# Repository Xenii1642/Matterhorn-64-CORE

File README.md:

Matterhorn 64 CORE is the world's smallest open-source Nintendo 64 motherboard redesign. 
It utilizes components taken from an original Nintendo 64 console. 
Because it does **not** rely on emulation, it works perfectly with all games released on the system. 

This board redesign enables smaller, better, cleaner and more reliable Nintendo 64 based builds. 
Matterhorn 64 CORE can easily be integrated in different kinds of builds such as Nintendo 64 portable devices or mini consoles. 

It is fully open-source and released under the CERN-OHL-S-2.0 license. 

## Features
The Matterhorn 64 CORE redesign:
- The world's smallest open source Nintendo 64 motherboard
- Fits in a tiny 78x77.2 mm form factor 
- Runs on real hardware, **no emulation**
- 100% compatible with **all** games released on the system, including flashcarts
- Runs on 3.3V @2A 
- Designed using KiCad 9
- Layout and routing is optimized and clean, making it easy to use in future Nintendo 64 builds
- 100% open-source and released under the CERN-OHL-S-2.0 license

## Compatibility
### General compatibility
Due to the complexity of the Nintendo 64 hardware, some of its features are not available on this design. 
Please note that:
- The console is compatible with both NTSC and PAL components. However, it is **NOT** region free. It will only accept games released on the same region as the donor board.
- The console does accept memory expansion, but it is not natively compatible with the orignal Expansion Pak cartridge. You'll need to solder two RDRAM36 4MB instead of the two RDRAM18 2MB chips present by default on the console in order to enable the Expansion Pak.
- The console does **NOT** have any video output system. You'll either need to hook up an original composite encoder compatible with your region or an HDMI kit.
- The console does **NOT** have on-board voltage regulators. An additional N64 PSU or 3.3V PSU will be needed in order to use it. The console requires only requires 3.3V at 2A, but please consider that some HDMI mod or composite encoders may require 5V as well.
- The console is compatible with original controllers.
- It is also compatible with original cartridges using the breakout board.

### Nintendo 64 donor board revision compatibility
This mod is **ONLY** compatible with the following motherboard revisions:
#### NTSC Revisions (North America and Japan)
- NUS-CPU-01 (Japan only - 1996)
- NUS-CPU-02 (1996)
- NUS-CPU-03 (1996)
- NUS-CPU-04 (1996-1997)
- NUS-CPU-05 (1997)
- NUS-CPU-05-1 (1997)
- NUS-CPU-06 (1998)
- NUS-CPU-07 (1998)

#### PAL REVISION (Europe and Australia)
- NUS-CPU(P)-01 (1996)
- NUS-CPU(R)-01 (France only - 1997)

**ANY NEWER REVISION WILL NOT BE COMPATIBLE**

## Disclamer
This project requires complex soldering techniques. It relies on small pitch QFPs and 0402 passives.
Removing the components from the original board can cause irreparable damage if done incorrectly.

Due to the nature of this project, I am not responsible for any physical damages that may occur. 

## PCB Files
The Matterhorn 64 CORE motherboard has been entirely designed using KiCad 9. 
All the files are available in the [KiCad files folder](https://github.com/Xenii1642/Matterhorn-64-CORE/tree/main/KiCad%20Files) of this repository. 
The libraries created are also available in that same folder. 

Gerbers can be found in the [Gerber folder](https://github.com/Xenii1642/Matterhorn-64-CORE/tree/main/Gerbers). 

The console needs those two PCBs in order to make it work:
- [Matterhorn 64 CORE redesign](https://github.com/Xenii1642/Matterhorn-64-CORE/blob/main/Gerbers/Matterhorn-64-CORE.zip)
- [Matterhorn Cartridge Breakout](https://github.com/Xenii1642/Matterhorn-64-CORE/blob/main/Gerbers/Cartridge-Breakout-Board.zip)

The CORE itself represents the main logic of the console. The breakout board is used easily connect a full size game cartridge to the console. 

## Ordering
For this project, I recommend ordering the board through [JLCPCB](https://jlcpcb.com/) or [PCBWay](https://pcbway.com/). 
I personally ordered mine through [JLCPCB](https://jlcpcb.com/). 

You'll find here the list of settings that must be applied when ordering. 

### [Matterhorn 64 CORE](https://github.com/Xenii1642/Matterhorn-64-CORE/blob/main/Gerbers/Matterhorn-64-CORE.zip)
- Material: FR4
- Layers: 4
- Thickness: 1.6mm
- Specify Stackup: YES - JLC04161H-3313
- Impedance Control: ±10%
- Stencil: recommended but not obligatory.

### [Matterhorn Cartridge Breakout](https://github.com/Xenii1642/Matterhorn-64-CORE/blob/main/Gerbers/Cartridge-Breakout-Board.zip)
- Material: FR4
- Layers: 2

### Board Impedance Control
As you might notice, the CORE requires controlled impedance. 
The Nintendo 64 uses an extremely fast Rambus Dynamic Random Access Memory Bus (RDRAM BUS). 
In order to work, the CORE requires controlled impedance to match the 50Ω required by the RDRAM BUS. 

The Gerber files for this board include an Excel document which specifies which traces require those controlled impedance. 
This document will only be taken into account by JLCPCB if the order specifies the use of the "Controlled Impedance" option set to ±10%.

Please note that the board **might** work by using the 3313 stackup with no controlled impedance. 
To make sure my prototype was working, I did order it using those specifications. 
Ordering without it has not been tried and is at your own risks. 

All the components are listed in the Bill Of Materials (BOM). They can be ordered through Digikey or Mouser. 

## Assembly 
Once you've sourced a working Nintendo 64 console, a few games to test it, all the components and the Matterhorn 64 CORE boards, assembly can begin!
First of all, you'll need to access the Nintendo 64 motherboard and remove these components:
- CPU-NUS (U10)
- RCP-NUS (U9)
- 2x RDRAM18-NUS (U14 & U11) (or 1x RDRAM36 depending of the version, U14)) 
- NUS-PIF (U6)
- PTS9128 (U3)
- 74LCV125 (U8)
- 2x MX8330 (U7 & U15)
- 2x Crystals (X1 & X2)
- Sharp 7VZ5 LDO (U12)
- Cartridge slot (P5)

Source of this image: Wikipedia.com

I personally removed mine using hot air and a bit of flux. I heated at 360°C. 
Once removed, they can take place on the new motherboard. 
Low melting solder is not recommended in this process since the board will heat and cool down constantly when running, which can damage the solder joints after a long time. It is also not recommended to heat either the board or the components too much, which could lead to issues. 
I recommend soldering the whole front side and then solder the back side. 

The breakout board is much simpler, it only has a single FFC connector and the cartridge slot, which are much easier to solder than the little passives in my opinion. 

Once everything is done and cleaned using isopropyl alcohol, the test process can begin!

## Testing
First, connect the breakout board and make sure you don't have any dead shorts between the 3.3V line and the GND. 
Then, insert a game and power it up! The board is properly powered if:
- The console draws roughly 1.4A
- Vterm shows 2.55V
- Vref shows 1.91V

If you own a logic analyzer, you can connect it to the audio data pins or controller ports.
This is what you should see on the controller data line when a controller is plugged on Super Mario 64

Please note that those signals **DO NOT** appear if the game is not properly read.
If everything seems good, you can hook up an HDMI mod or composite encoder and test it out! If it displays, it works! Great job!

## Known issue:
When I assembled my prototype, I *probably* heated the CPU too much while removing it. This caused the console to only work if heated.
More tests will be done to understand what exactly caused that. 

However I want to mention that the board works flawlessly for multiple consecutive days. 

## Future projects
This board is my official entry into Nintendo 64 modding. 
I'm working on two big projects which both use the CORE:
- Weisshorn 64 Mini: A collab between SenorAvocado and the Xii-Labs to create a Nintendo 64 Classic Mini console.
- Matterhorn 64: An ultimate Nintendo 64 portable. It's going to be a true revolution, also powered by the core.

Going to keep everyone update through my socials and the BitBuilt server. 

## Credits
This project was the most complicated I've done. Thankfully some members of the BitBuilt community helped me out to make my journey easier.
Therefore, I wanted to address big thanks to:
- @cy-888 who collaborated with me on some part of the design, especially footprints
- @CrazyGadgetMods who made great open-source flexes which helped me understanding some part of the console
- @mackieks who answered all my technical questions and took the time to review the whole board
- @thedrew and @gunnar who gave me insiparation to design my own motherboard recreation as long as helping me throughout the process.

## Media
You can find a video of my working board on my Instagram account:
[Matterhorn 64 CORE testing video](https://www.instagram.com/reel/DWvlAQKiPuf/)

I've also considered making a longer YouTube video on the subject. I will probably do it when I have more time.
## License
Matterhorn 64 CORE is released under the CERN-OHL-S-2.0 license. 
This license allows you to:
- Study
- Modify
- Manufacture
- Sell
- Distribute

Any modified versions of derivatives must also remain open-source under **the same, unmodified license**
You must also properly credit the original creators when reusing or redistributing these files.

## Support
If you notice anything wrong with the design, please let me know!
You can also reach to me for questions or general help, I'm always happy to help 👍

Thank you for your support and see you next time!

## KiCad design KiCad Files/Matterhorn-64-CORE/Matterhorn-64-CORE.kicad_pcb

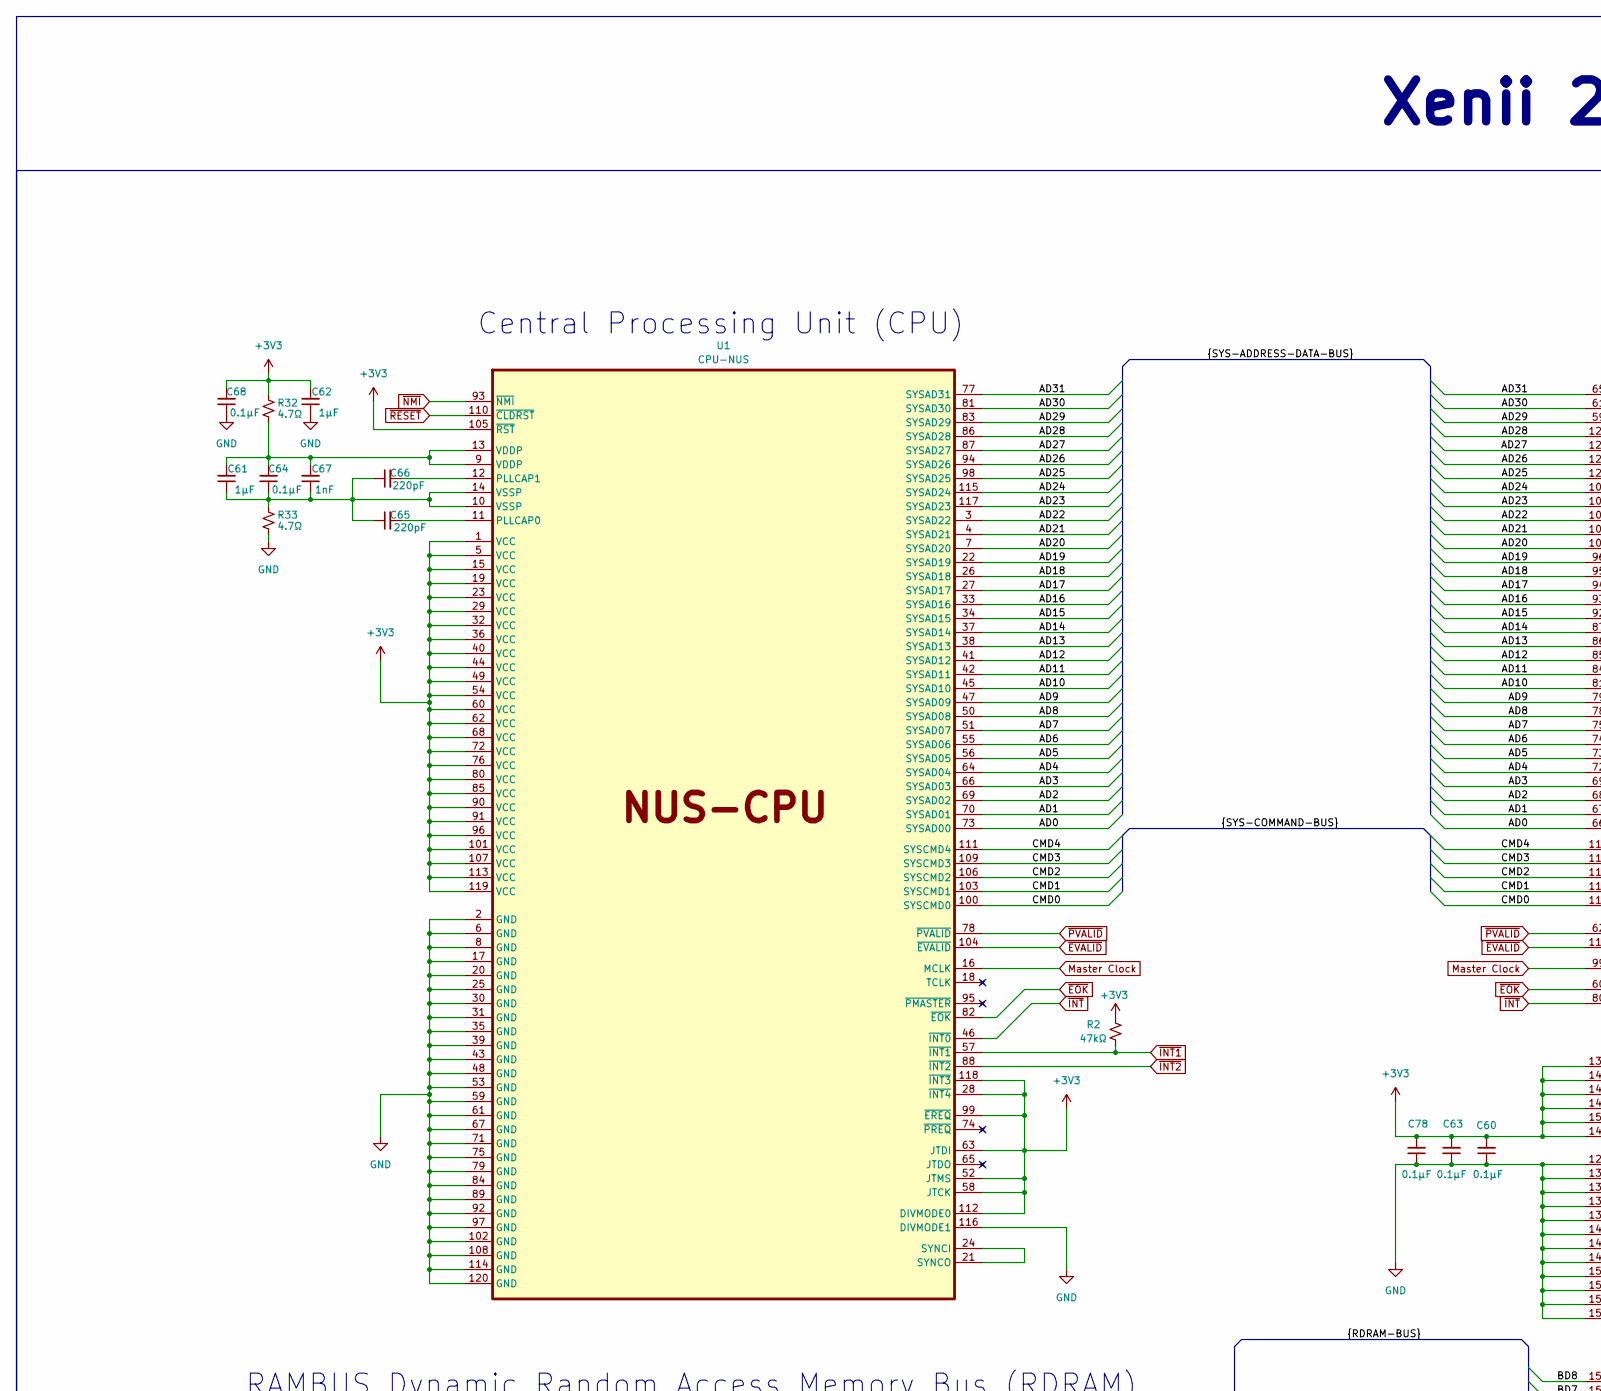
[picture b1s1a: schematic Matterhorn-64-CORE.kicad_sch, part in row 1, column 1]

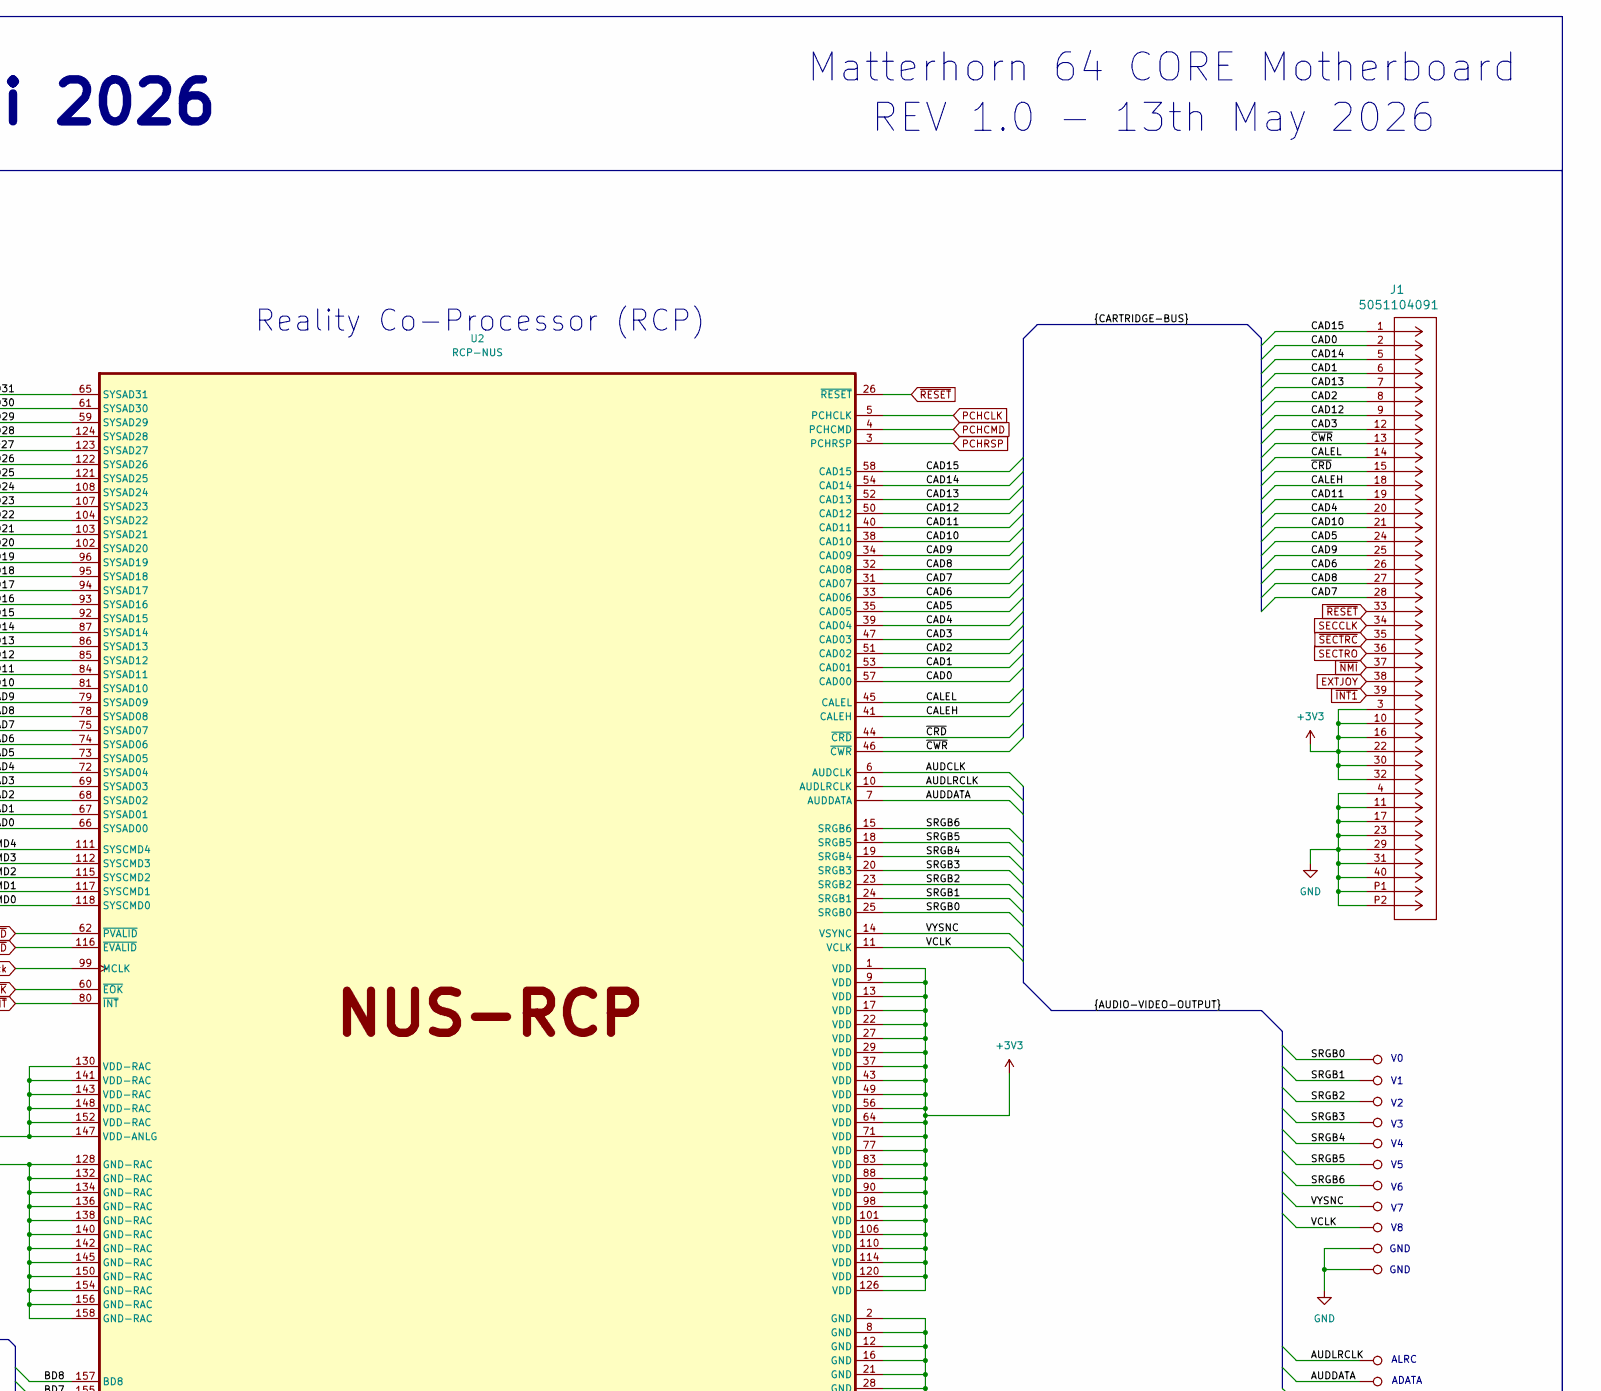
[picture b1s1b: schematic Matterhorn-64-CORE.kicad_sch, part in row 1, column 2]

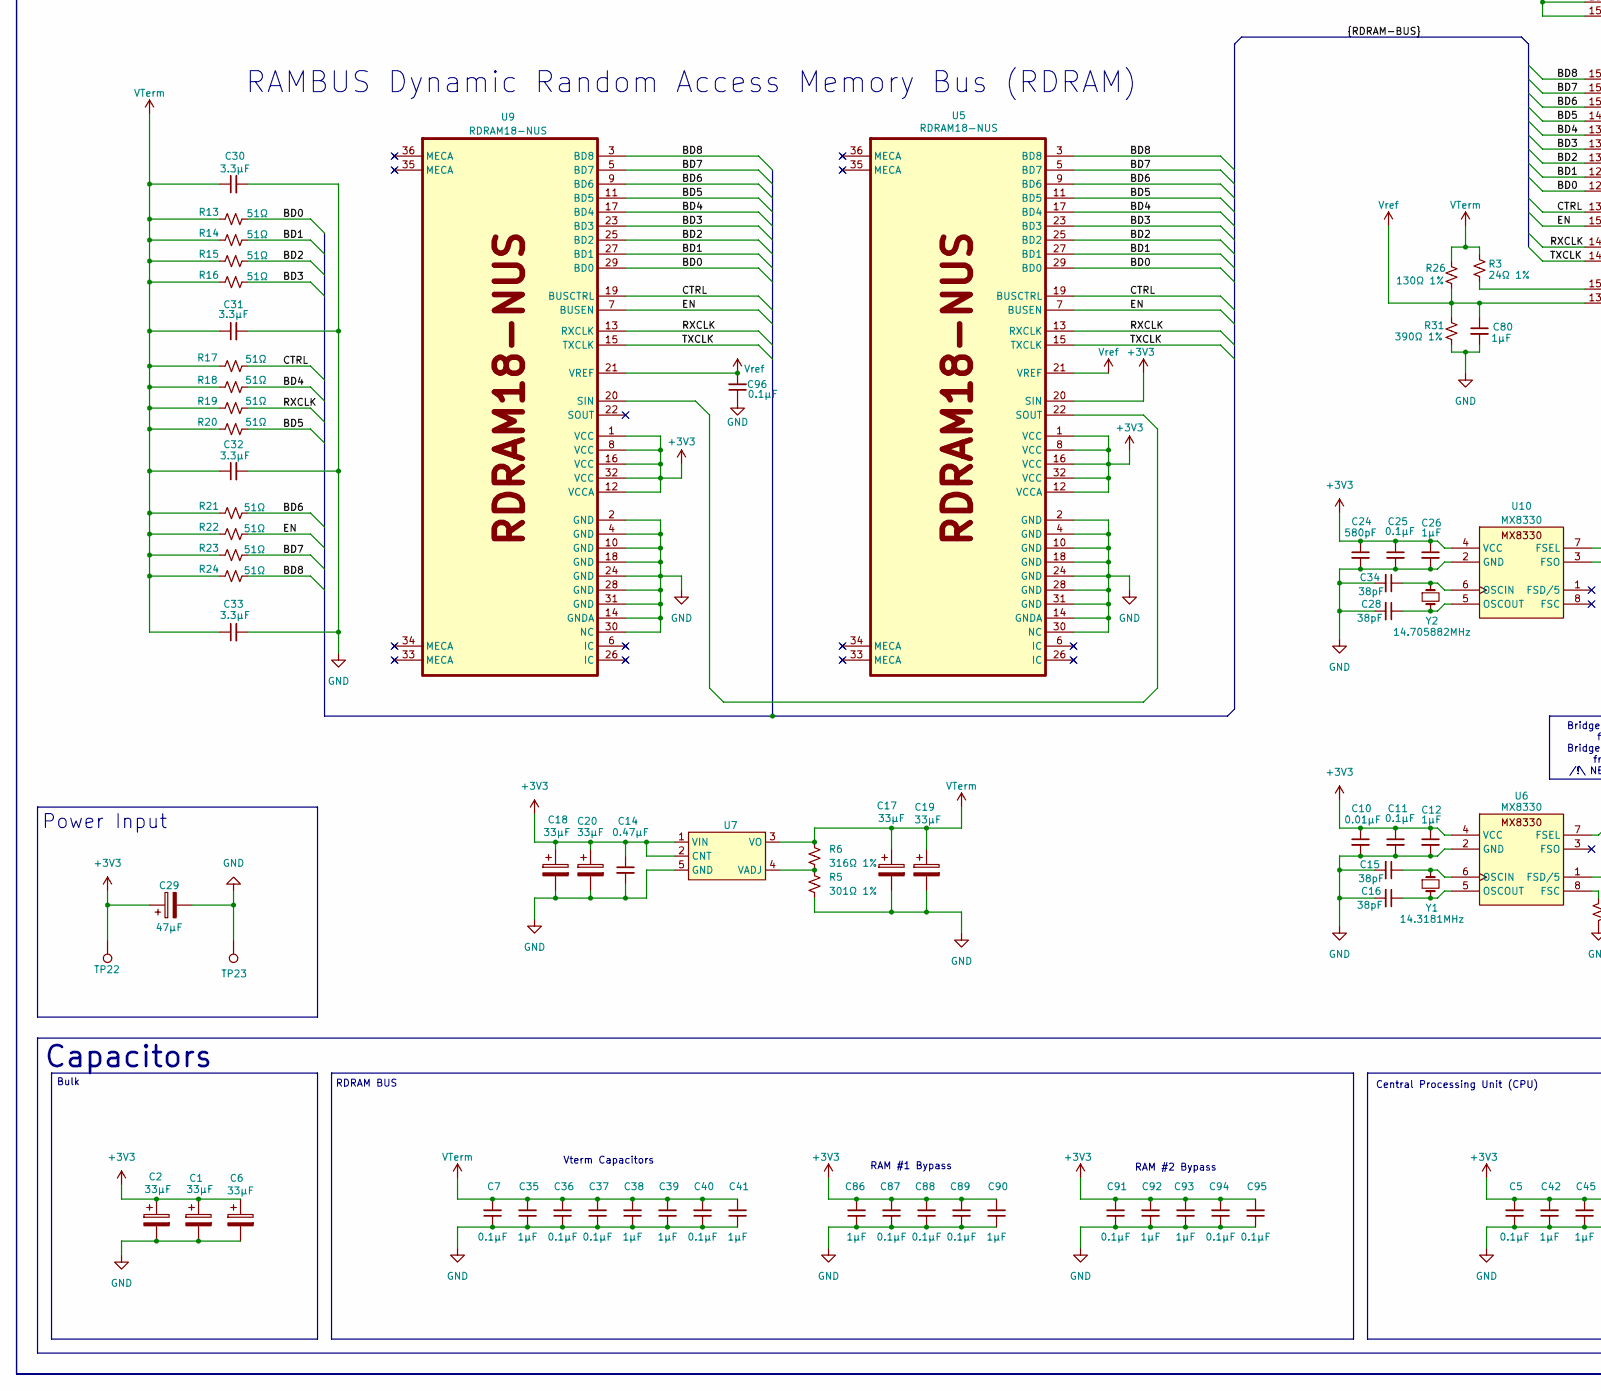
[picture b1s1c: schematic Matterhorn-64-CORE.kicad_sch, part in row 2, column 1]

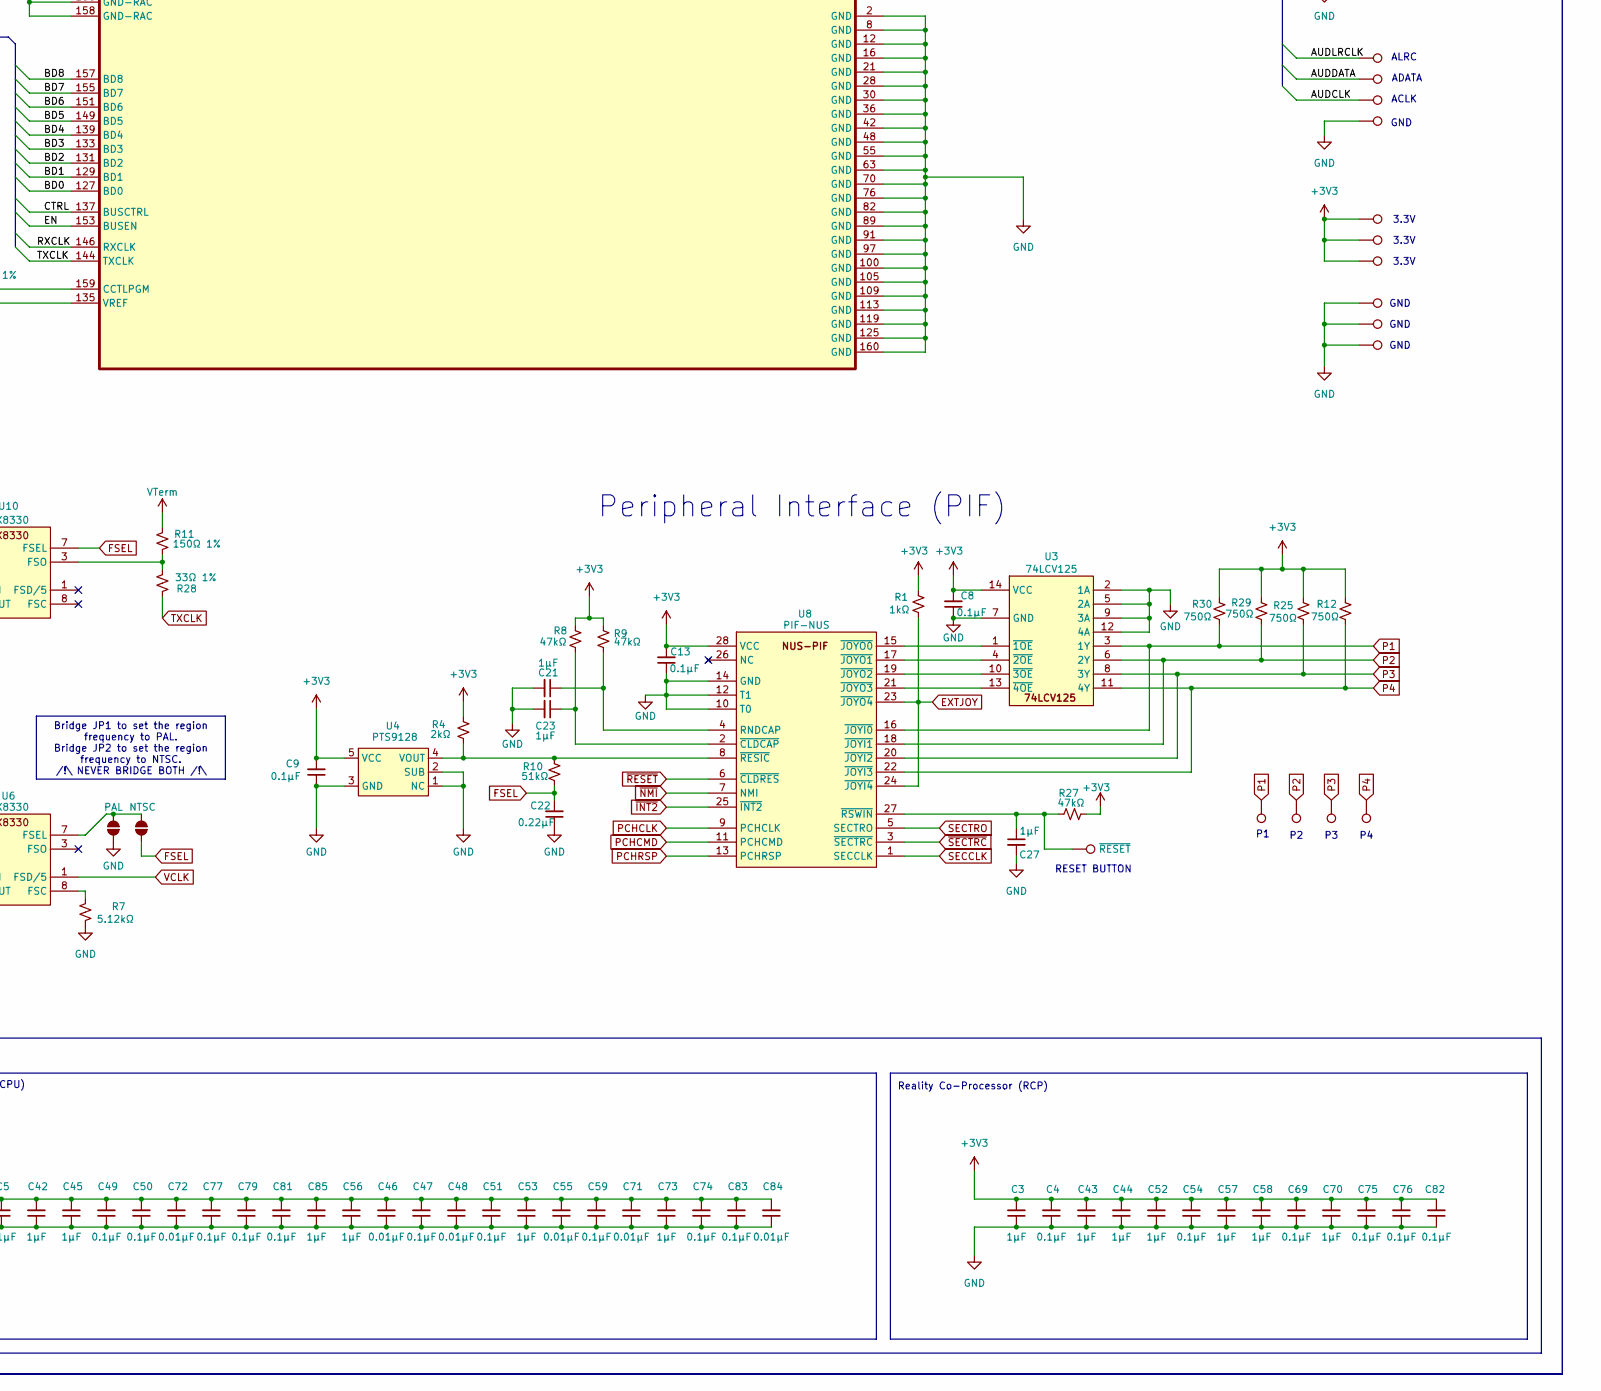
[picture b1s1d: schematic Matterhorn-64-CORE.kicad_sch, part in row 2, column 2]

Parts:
C1, C2, C6, C17, C18, C19, C20: 33µF; TAJB_AVX-M
C3, C12, C21, C23, C26, C27, C35, C38, C39, C41, C42, C43, C44, C45, C52, C53, C56, C57, C58, C61, C62, C70, C73, C80, C85, C86, C90, C92, C93: 1µF; C_0402_1005Metric
C4, C5, C7, C8, C9, C11, C13, C25, C36, C37, C40, C47, C49, C50, C51, C54, C59, C60, C63, C64, C68, C69, C74, C75, C76, C77, C78, C79, C81, C82, C83, C87, C88, C89, C91, C94, C95, C96: 0.1µF; C_0402_1005Metric
C10, C46, C48, C55, C71, C72, C84: 0.01µF; C_0402_1005Metric
C14: 0.47µF; C_0402_1005Metric
C15, C16, C28, C34: 38pF; C_0402_1005Metric
C22: 0.22µF; C_0402_1005Metric
C24: 580pF; C_0402_1005Metric
C29: 47µF; 865080442004
C30, C31, C32, C33: 3.3µF; C_0402_1005Metric
C65, C66: 220pF; C_0402_1005Metric
C67: 1nF; C_0402_1005Metric
J1: 5051104091; CON_5051104091_MOL
NTSC: NTSC; SolderJumper-2_P1.3mm_Open_RoundedPad1.0x1.5mm
PAL: PAL; SolderJumper-2_P1.3mm_Open_RoundedPad1.0x1.5mm
R1: 1kΩ; R_0402_1005Metric
R2, R8, R9, R27: 47kΩ; R_0402_1005Metric
R3: 24Ω 1%; R_0402_1005Metric
R4: 2kΩ; R_0402_1005Metric
R5: 301Ω 1%; R_0402_1005Metric
R6: 316Ω 1%; R_0402_1005Metric
R7: 5.12kΩ; R_0402_1005Metric
R10: 51kΩ; R_0402_1005Metric
R11: 150Ω 1%; R_0402_1005Metric
R12, R25, R29, R30: 750Ω; R_0402_1005Metric
R13, R14, R15, R16, R17, R18, R19, R20, R21, R22, R23, R24: 51Ω; R_0402_1005Metric
R26: 130Ω 1%; R_0805_2012Metric
R28: 33Ω 1%; R_0402_1005Metric
R31: 390Ω 1%; R_0805_2012Metric
R32, R33: 4.7Ω; R_0402_1005Metric
RST1, RST2, RST3, RST4: TestPoint; TestPoint_Pad_D1.0mm
TP1, TP2, TP3, TP4, TP5, TP6, TP7, TP8, TP9, TP10, TP11, TP12, TP13, TP14, TP15, TP16, TP17, TP18, TP19, TP20, TP21: TestPoint; TestPoint_Pad_D1.0mm
TP22, TP23: TestPoint; PowerPad
U1: CPU-NUS
U2: RCP-NUS
U3: 74LCV125
U4: PTS9128; SOT-23-5
U5, U9: RDRAM18-NUS
U6, U10: MX8330
U7: SHARP 7VZ5
U8: PIF-NUS
Y1: 14.3181MHz; Crystal
Y2: 14.705882MHz; Crystal
~{RESET}: TestPoint; TestPoint_Pad_D1.0mm

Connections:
+3V3: C1.1, C2.1, C3.2, C4.2, C5.2, C6.1, C8.2, C9.2, C10.1, C11.1, C12.1, C13.2, C14.1, C18.1, C20.1, C24.1, C25.1, C26.1, C29.1, C42.2, C43.2, C44.2, C45.2, C46.2, C47.2, C48.2, C49.2, C50.2, C51.2, C52.2, C53.2, C54.2, C55.2, C56.2, C57.2, C58.2, C59.2, C60.2, C62.2, C63.2, C68.2, C69.2, C70.2, C71.2, C72.2, C73.2, C74.2, C75.2, C76.2, C77.2, C78.2, C79.2, C81.2, C82.2, C83.2, C84.2, C85.2, C86.2, C87.2, C88.2, C89.2, C90.2, C91.2, C92.2, C93.2, C94.2, C95.2, J1.3, J1.10, J1.16, J1.22, J1.30, J1.32, R1.1, R2.1, R4.2, R8.2, R9.2, R12.1, R25.1, R27.1, R29.1, R30.1, R32.1, TP19.1, TP20.1, TP21.1, TP22.1, U1.1 (VCC), U1.5 (VCC), U1.15 (VCC), U1.19 (VCC), U1.23 (VCC), U1.28 (~INT4), U1.29 (VCC), U1.32 (VCC), U1.36 (VCC), U1.40 (VCC), U1.44 (VCC), U1.49 (VCC), U1.52 (JTMS), U1.54 (VCC), U1.58 (JTCK), U1.60 (VCC), U1.62 (VCC), U1.63 (JTDI), U1.68 (VCC), U1.72 (VCC), U1.76 (VCC), U1.80 (VCC), U1.85 (VCC), U1.90 (VCC), U1.91 (VCC), U1.96 (VCC), U1.99 (~EREQ), U1.101 (VCC), U1.105 (~RST), U1.107 (VCC), U1.112 (DIVMODE0), U1.113 (VCC), U1.118 (~INT3), U1.119 (VCC), U2.1 (VDD), U2.9 (VDD), U2.13 (VDD), U2.17 (VDD), U2.22 (VDD), U2.27 (VDD), U2.29 (VDD), U2.37 (VDD), U2.43 (VDD), U2.49 (VDD), U2.56 (VDD), U2.64 (VDD), U2.71 (VDD), U2.77 (VDD), U2.83 (VDD), U2.88 (VDD), U2.90 (VDD), U2.98 (VDD), U2.101 (VDD), U2.106 (VDD), U2.110 (VDD), U2.114 (VDD), U2.120 (VDD), U2.126 (VDD), U2.130 (VDD-RAC), U2.141 (VDD-RAC)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
/AD0: U1.73 (SYSAD00), U2.66 (SYSAD00)
/AD1: U1.70 (SYSAD01), U2.67 (SYSAD01)
/AD2: U1.69 (SYSAD02), U2.68 (SYSAD02)
/AD3: U1.66 (SYSAD03), U2.69 (SYSAD03)
/AD4: U1.64 (SYSAD04), U2.72 (SYSAD04)
/AD5: U1.56 (SYSAD05), U2.73 (SYSAD05)
/AD6: U1.55 (SYSAD06), U2.74 (SYSAD06)
/AD7: U1.51 (SYSAD07), U2.75 (SYSAD07)
/AD8: U1.50 (SYSAD08), U2.78 (SYSAD08)
/AD9: U1.47 (SYSAD09), U2.79 (SYSAD09)
/AD10: U1.45 (SYSAD10), U2.81 (SYSAD10)
/AD11: U1.42 (SYSAD11), U2.84 (SYSAD11)
/AD12: U1.41 (SYSAD12), U2.85 (SYSAD12)
/AD13: U1.38 (SYSAD13), U2.86 (SYSAD13)
/AD14: U1.37 (SYSAD14), U2.87 (SYSAD14)
/AD15: U1.34 (SYSAD15), U2.92 (SYSAD15)
/AD16: U1.33 (SYSAD16), U2.93 (SYSAD16)
/AD17: U1.27 (SYSAD17), U2.94 (SYSAD17)
/AD18: U1.26 (SYSAD18), U2.95 (SYSAD18)
/AD19: U1.22 (SYSAD19), U2.96 (SYSAD19)
/AD20: U1.7 (SYSAD20), U2.102 (SYSAD20)
/AD21: U1.4 (SYSAD21), U2.103 (SYSAD21)
/AD22: U1.3 (SYSAD22), U2.104 (SYSAD22)
/AD23: U1.117 (SYSAD23), U2.107 (SYSAD23)
/AD24: U1.115 (SYSAD24), U2.108 (SYSAD24)
/AD25: U1.98 (SYSAD25), U2.121 (SYSAD25)
/AD26: U1.94 (SYSAD26), U2.122 (SYSAD26)
/AD27: U1.87 (SYSAD27), U2.123 (SYSAD27)
/AD28: U1.86 (SYSAD28), U2.124 (SYSAD28)
/AD29: U1.83 (SYSAD29), U2.59 (SYSAD29)
/AD30: U1.81 (SYSAD30), U2.61 (SYSAD30)
/AD31: U1.77 (SYSAD31), U2.65 (SYSAD31)
/AUDCLK: TP14.1, U2.6 (AUDCLK)
/AUDDATA: TP13.1, U2.7 (AUDDATA)
/AUDLRCLK: TP12.1, U2.10 (AUDLRCLK)
/BD0: R13.1, U2.127 (BD0), U5.29 (BD0), U9.29 (BD0)
/BD1: R14.1, U2.129 (BD1), U5.27 (BD1), U9.27 (BD1)
/BD2: R15.1, U2.131 (BD2), U5.25 (BD2), U9.25 (BD2)
/BD3: R16.1, U2.133 (BD3), U5.23 (BD3), U9.23 (BD3)
/BD4: R18.1, U2.139 (BD4), U5.17 (BD4), U9.17 (BD4)
/BD5: R20.1, U2.149 (BD5), U5.11 (BD5), U9.11 (BD5)
/BD6: R21.1, U2.151 (BD6), U5.9 (BD6), U9.9 (BD6)
/BD7: R23.1, U2.155 (BD7), U5.5 (BD7), U9.5 (BD7)
/BD8: R24.1, U2.157 (BD8), U5.3 (BD8), U9.3 (BD8)
/CAD0: J1.2, U2.57 (CAD00)
/CAD1: J1.6, U2.53 (CAD01)
/CAD2: J1.8, U2.51 (CAD02)
/CAD3: J1.12, U2.47 (CAD03)
/CAD4: J1.20, U2.39 (CAD04)
/CAD5: J1.24, U2.35 (CAD05)
/CAD6: J1.26, U2.33 (CAD06)
/CAD7: J1.28, U2.31 (CAD07)
/CAD8: J1.27, U2.32 (CAD08)
/CAD9: J1.25, U2.34 (CAD09)
/CAD10: J1.21, U2.38 (CAD10)
/CAD11: J1.19, U2.40 (CAD11)
/CAD12: J1.9, U2.50 (CAD12)
/CAD13: J1.7, U2.52 (CAD13)
/CAD14: J1.5, U2.54 (CAD14)
/CAD15: J1.1, U2.58 (CAD15)
/CALEH: J1.18, U2.41 (CALEH)
/CALEL: J1.14, U2.45 (CALEL)
/CMD0: U1.100 (SYSCMD0), U2.118 (SYSCMD0)
/CMD1: U1.103 (SYSCMD1), U2.117 (SYSCMD1)
/CMD2: U1.106 (SYSCMD2), U2.115 (SYSCMD2)
/CMD3: U1.109 (SYSCMD3), U2.112 (SYSCMD3)
/CMD4: U1.111 (SYSCMD4), U2.111 (SYSCMD4)
/CTRL: R17.1, U2.137 (BUSCTRL), U5.19 (BUSCTRL), U9.19 (BUSCTRL)
/EN: R22.1, U2.153 (BUSEN), U5.7 (BUSEN), U9.7 (BUSEN)
/RXCLK: R19.1, U2.146 (RXCLK), U5.13 (RXCLK), U9.13 (RXCLK)
/SRGB0: TP2.1, U2.25 (SRGB0)
/SRGB1: TP3.1, U2.24 (SRGB1)
/SRGB2: TP4.1, U2.23 (SRGB2)
/SRGB3: TP5.1, U2.20 (SRGB3)
/SRGB4: TP6.1, U2.19 (SRGB4)
/SRGB5: TP7.1, U2.18 (SRGB5)
/SRGB6: TP8.1, U2.15 (SRGB6)
/VYSNC: TP9.1, U2.14 (VSYNC)
/~CRD: J1.15, U2.44 (~CRD)
/~CWR: J1.13, U2.46 (~CWR)
EXTJOY: J1.38, R1.2, U8.23 (~JOYO4), U8.24 (~JOYI4)
FSEL: C22.2, NTSC.1 (A), R10.1, U10.7 (FSEL)
GND: C1.2, C2.2, C3.1, C4.1, C5.1, C6.2, C7.1, C8.1, C9.1, C10.2, C11.2, C12.2, C13.1, C14.2, C15.2, C16.2, C17.2, C18.2, C19.2, C20.2, C21.2, C22.1, C23.2, C24.2, C25.2, C26.2, C27.2, C28.2, C29.2, C30.2, C31.2, C32.2, C33.2, C34.2, C35.1, C36.1, C37.1, C38.1, C39.1, C40.1, C41.1, C42.1, C43.1, C44.1, C45.1, C46.1, C47.1, C48.1, C49.1, C50.1, C51.1, C52.1, C53.1, C54.1, C55.1, C56.1, C57.1, C58.1, C59.1, C60.1, C62.1, C63.1, C68.1, C69.1, C70.1, C71.1, C72.1, C73.1, C74.1, C75.1, C76.1, C77.1, C78.1, C79.1, C80.2, C81.1, C82.1, C83.1, C84.1, C85.1, C86.1, C87.1, C88.1, C89.1, C90.1, C91.1, C92.1, C93.1, C94.1, C95.1, C96.1, J1.4, J1.11, J1.17, J1.23, J1.29, J1.31, J1.40, J1.P1, J1.P2, PAL.1 (A), R5.2, R7.2, R31.1, R33.2, TP1.1, TP11.1, TP15.1, TP16.1, TP17.1, TP18.1, TP23.1, U1.2 (GND), U1.6 (GND), U1.8 (GND), U1.17 (GND), U1.20 (GND), U1.25 (GND), U1.30 (GND), U1.31 (GND), U1.35 (GND), U1.39 (GND), U1.43 (GND), U1.48 (GND), U1.53 (GND), U1.59 (GND), U1.61 (GND), U1.67 (GND), U1.71 (GND), U1.75 (GND), U1.79 (GND), U1.84 (GND), U1.89 (GND), U1.92 (GND), U1.97 (GND), U1.102 (GND), U1.108 (GND), U1.114 (GND), U1.116 (DIVMODE1), U1.120 (GND), U2.2 (GND), U2.8 (GND), U2.12 (GND), U2.16 (GND), U2.21 (GND), U2.28 (GND), U2.30 (GND), U2.36 (GND)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
Master Clock: U1.16 (MCLK), U2.99 (MCLK)
unnamed: C61.1, C64.1, C65.1, C66.1, C67.1, R33.1, U1.10 (VSSP), U1.14 (VSSP)
unnamed: C61.2, C64.2, C67.2, R32.2, U1.9 (VDDP), U1.13 (VDDP)
unnamed: NTSC.2 (B), PAL.2 (B), U6.7 (FSEL)
unnamed: C65.2, U1.11 (PLLCAP0)
unnamed: C66.2, U1.12 (PLLCAP1)
unnamed: U1.21 (SYNCO), U1.24 (SYNCI)
unnamed: R3.1, U2.159 (CCTLPGM)
unnamed: U3.1 (~1OE), U8.15 (~JOYO0)
unnamed: U3.4 (~2OE), U8.17 (~JOYO1)
unnamed: U3.10 (~3OE), U8.19 (~JOYO2)
unnamed: U3.13 (~4OE), U8.21 (~JOYO3)
unnamed: R4.1, R10.2, U4.4 (VOUT), U8.8 (~RESIC)
unnamed: U5.22 (SOUT), U9.20 (SIN)
unnamed: R7.1, U6.8 (FSC)
unnamed: C15.1, U6.6 (OSCIN), Y1.1
unnamed: C16.1, U6.5 (OSCOUT), Y1.2
unnamed: R5.1, R6.2, U7.4 (VADJ)
unnamed: C21.1, R9.1, U8.4 (RNDCAP)
unnamed: C23.1, R8.1, U8.2 (~CLDCAP)
unnamed: C27.1, R27.2, U8.27 (~RSWIN), ~{RESET}.1
unnamed: R11.2, R28.1, U10.3 (FSO)
unnamed: C34.1, U10.6 (OSCIN), Y2.1
unnamed: C28.1, U10.5 (OSCOUT), Y2.2
P1: R30.2, RST4.1, U3.3 (1Y), U8.16 (~JOYI0)
P2: R29.2, RST3.1, U3.6 (2Y), U8.18 (~JOYI1)
P3: R25.2, RST2.1, U3.8 (3Y), U8.20 (~JOYI2)
P4: R12.2, RST1.1, U3.11 (4Y), U8.22 (~JOYI3)
PCHCLK: U2.5 (PCHCLK), U8.9 (PCHCLK)
PCHCMD: U2.4 (PCHCMD), U8.11 (PCHCMD)
PCHRSP: U2.3 (PCHRSP), U8.13 (PCHRSP)
SECCLK: J1.34, U8.1 (SECCLK)
SECTRO: J1.36, U8.5 (SECTRO)
TXCLK: R28.2, U2.144 (TXCLK), U5.15 (TXCLK), U9.15 (TXCLK)
VCLK: TP10.1, U2.11 (VCLK), U6.1 (FSD/5)
VTerm: C7.2, C17.1, C19.1, C30.1, C31.1, C32.1, C33.1, C35.2, C36.2, C37.2, C38.2, C39.2, C40.2, C41.2, R3.2, R6.1, R11.1, R13.2, R14.2, R15.2, R16.2, R17.2, R18.2, R19.2, R20.2, R21.2, R22.2, R23.2, R24.2, R26.2, U7.3 (VO)
Vref: C80.1, C96.2, R26.1, R31.2, U2.135 (VREF), U5.21 (VREF), U9.21 (VREF)
~EOK: U1.82 (~EOK), U2.60 (~EOK)
~EVALID: U1.104 (~EVALID), U2.116 (~EVALID)
~INT1: J1.39, R2.2, U1.57 (~INT1)
~INT2: U1.88 (~INT2), U8.25 (~INT2)
~INT: U1.46 (~INT0), U2.80 (~INT)
~NMI: J1.37, U1.93 (~NMI), U8.7 (NMI)
~PVALID: U1.78 (~PVALID), U2.62 (~PVALID)
~RESET: J1.33, U1.110 (~CLDRST), U2.26 (~RESET), U8.6 (~CLDRES)
~SECTRC: J1.35, U8.3 (~SECTRC)

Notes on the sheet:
Reality Co-Processor (RCP)
RESET BUTTON
GND
ALRC
Bulk
3.3V
RAM #1 Bypass
RAMBUS Dynamic Random Access Memory Bus (RDRAM)
ADATA
Peripheral Interface (PIF)
Capacitors
Central Processing Unit (CPU)
RAM #2 Bypass
ACLK
Power Input
RDRAM BUS
Vterm Capacitors
Matterhorn 64 CORE Motherboard
REV 1.0 - 13th May 2026
Xenii 2026
Bridge JP1 to set the region frequency to PAL. Bridge JP2 to set the region frequency to NTSC. /!\ NEVER BRIDGE BOTH /!\

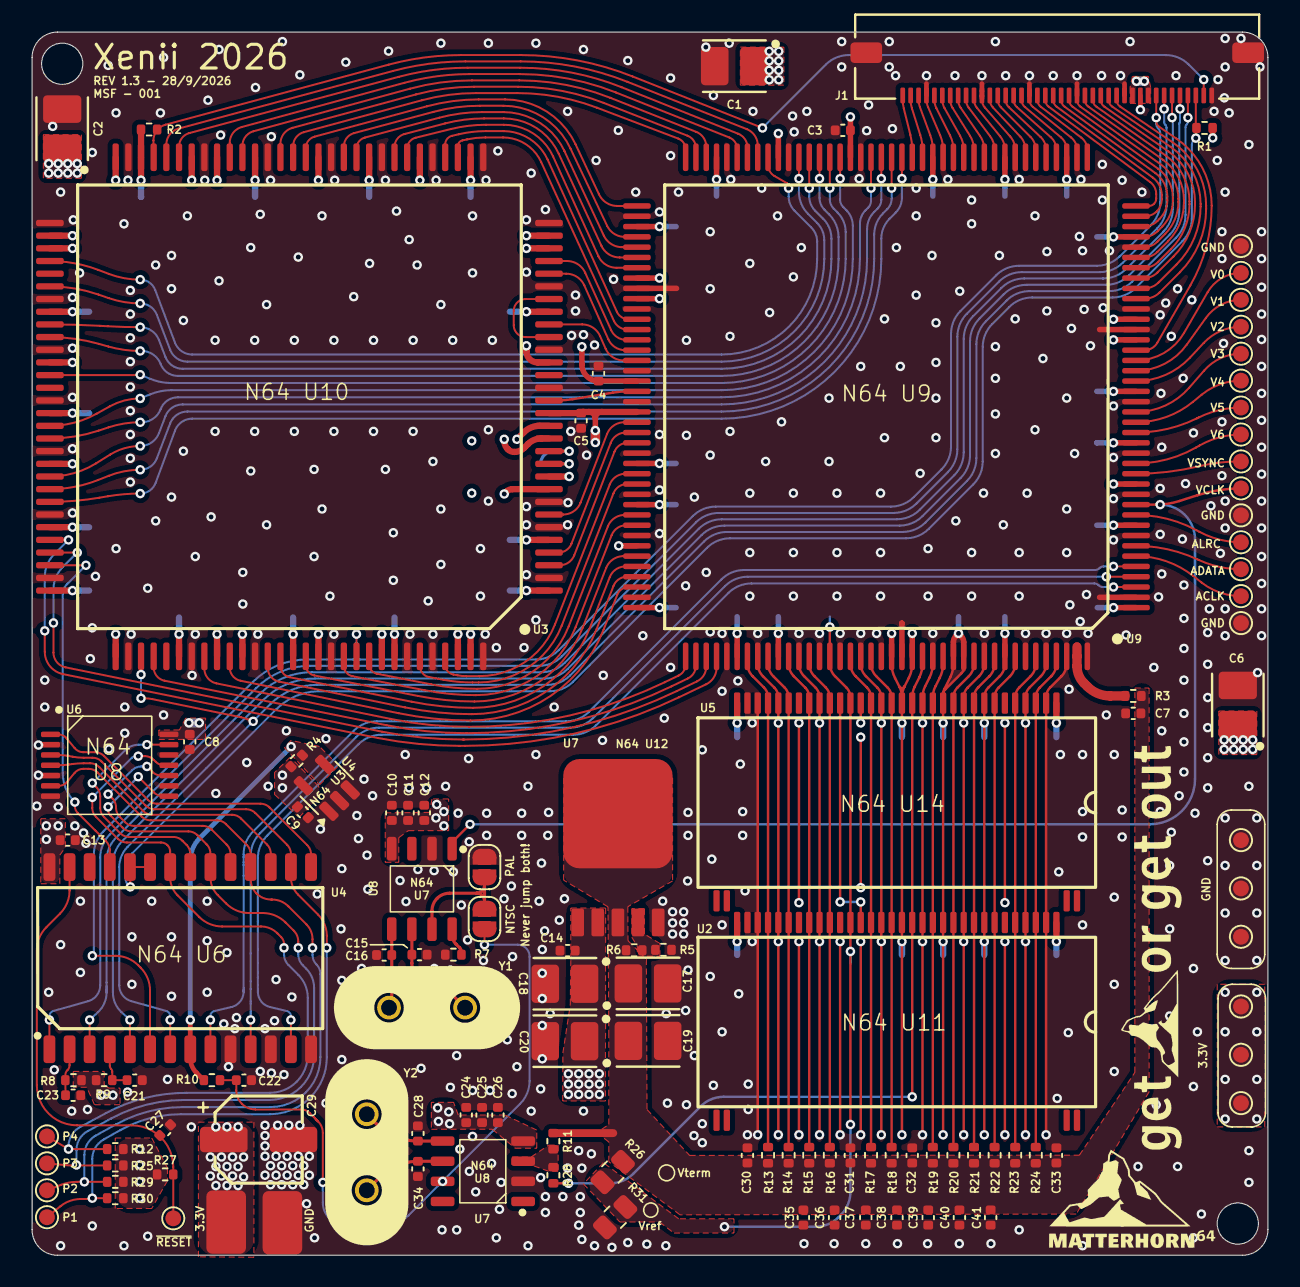
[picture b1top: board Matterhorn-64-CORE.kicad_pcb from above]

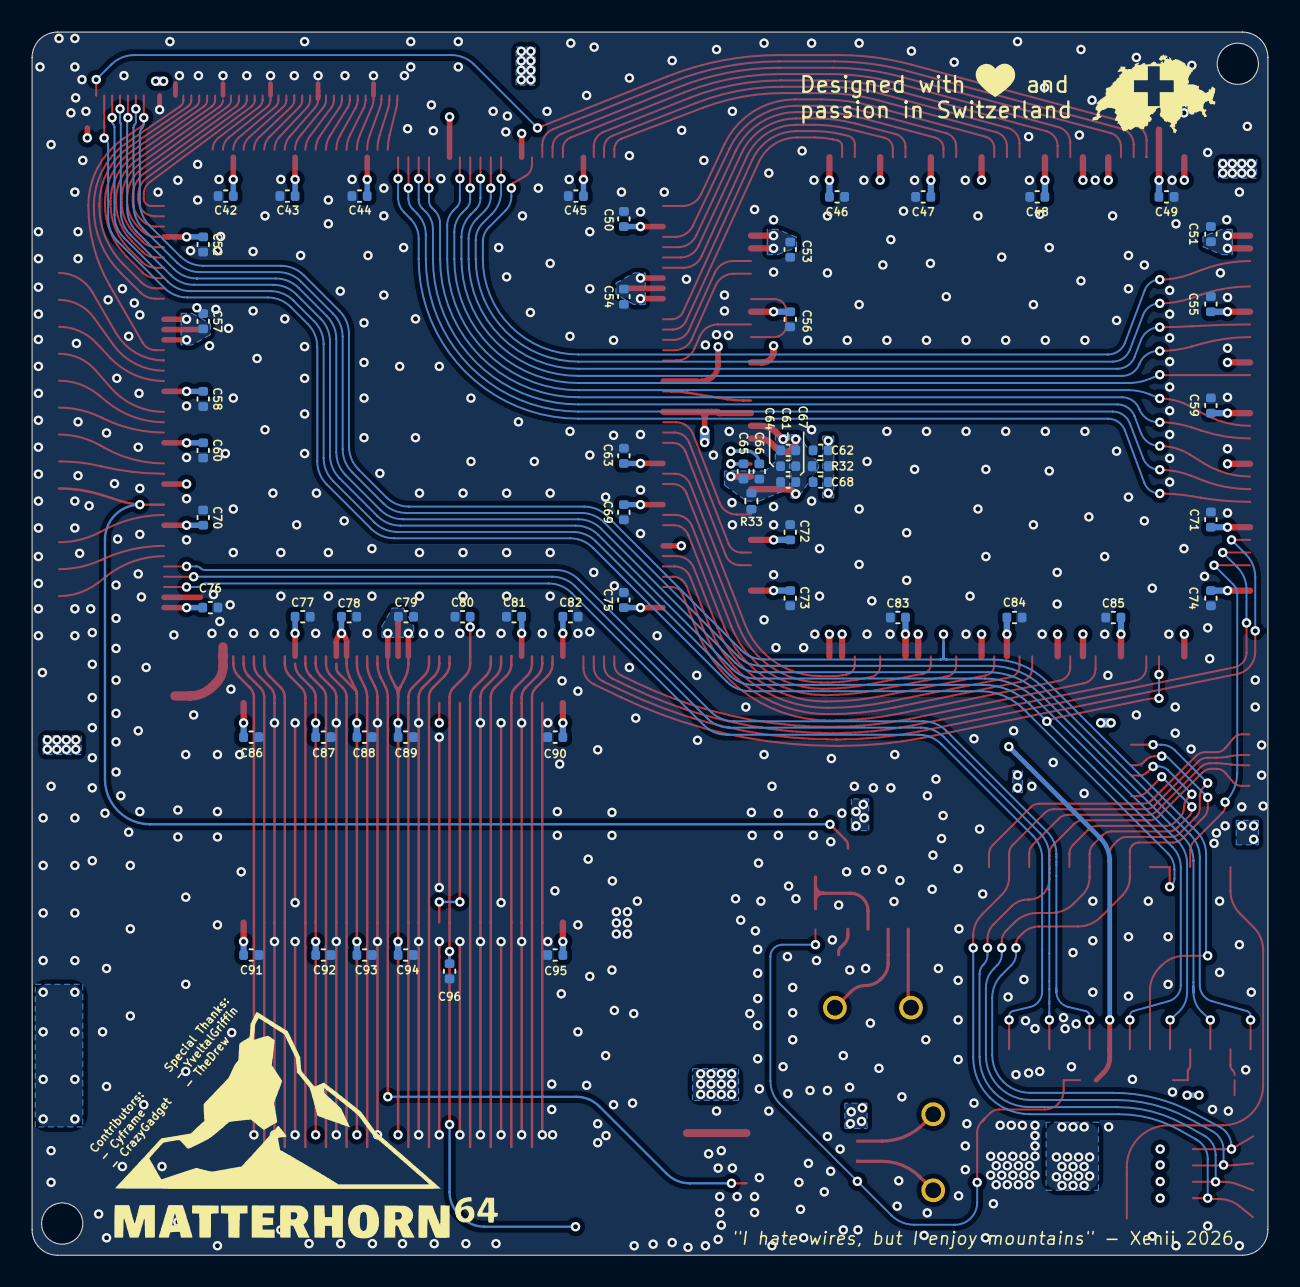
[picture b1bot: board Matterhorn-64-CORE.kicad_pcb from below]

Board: 4 copper layers, 78.0 x 77.2 mm, 171 parts (57 on the bottom side), 130 nets.

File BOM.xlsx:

Matterhorn 64 CORE BOM
CORE
Reference | Quantity | Value | Description | Manufacter Part Number | Link
C1,C2,C6,C17,C18,C19,C20 | 7 | 33µF | CAP TANT 33UF 10% 10V 1411 | TAJB336K010RNJ | https://www.digikey.com/en/products/detail/kyocera-avx/TAJB3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
C3,C12,C21,C23,C26,C27,C35, C38,C39,C41,C42,C43,C44,C45, C52,C53,C56,C57,C58,C6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 | 27 | 1µF | CAP CER 1UF 16V X5R 0402 | CL05A105KO5NNNC | https://www.digikey.com/en/products/detail/samsung-electro-m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
C4,C5,C7,C8,C9,C11,C13,C25,C36, C37,C40,C47,C49,C50,C51,C54,C59, C60,C63,C64,C6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 | 38 | 0.1µF | CAP CER 0.1UF 25V X5R 0402 | CL05A104KA5NNNC | https://www.digikey.com/en/products/detail/samsung-electro-m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
C10,C46,C48,C55,C71,C72,C84 | 7 | 0.01µF | CAP CER 10000PF 16V X7R 0402 | GRM155R71C103KA01D | https://www.digikey.com/en/products/detail/murata-electronic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
C14 | 1 | 0.47µF | CAP CER 0.47UF 10V X5R 0402 | C0402X5R100-474KNE-CT | https://www.digikey.com/en/products/detail/venkel/C0402X5R10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
C15,C16,C28,C34 | 4 | 38pF | CAP CER 39PF 50V C0G/NP0 0402 | C0402C390J5GACTU | https://www.digikey.com/en/products/detail/kemet/C0402C390J5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
C22 | 1 | 0.22µF | CAP CER 0.22UF 16V X7R 0402 | CL05B224KO5NNNC | https://www.digikey.com/en/products/detail/samsung-electro-m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
C24 | 1 | 560pF | CAP CER 560PF 50V C0G/NP0 0402 | GRM1555C1H561JA01D | https://www.digikey.com/en/products/detail/murata-electronic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
C29 | 1 | 47µF | CAP ALUM 47UF 20% 6.3V SMD | UCL0J470MCL1GS | https://www.digikey.com/en/products/detail/nichicon/UCL0J470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
C30,C31,C32,C33 | 4 | 3.3µF | CAP CER 3.3UF 4V X5R 0402 | C1005X5R0G335K050BB | https://www.digikey.com/en/products/detail/tdk-corporation/C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
C65,C66 | 2 | 220pF | CAP CER 220PF 25V X7R 0402 | C0402X7R250-221KNE-CT | https://www.digikey.com/en/products/detail/venkel/C0402X7R25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
C67 | 1 | 1nF | CAP CER 1000PF 50V X7R 0402 | C0402C102K5RACTU | https://www.digikey.com/en/products/detail/kemet/C0402C102K5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
J1 | 1 | 5051104091 | CONN FFC BOTTOM 40POS 0.5MM R/A | 5051104091 | https://www.digikey.com/en/products/detail/molex/5051104091/5254662
R1 | 1 | 1kΩ | RES 1K OHM 1% 1/16W 0402 | RC0402FR-131KL | https://www.digikey.com/en/products/detail/yageo/RC0402FR-13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
R2,R8,R9,R27 | 4 | 47kΩ | RES 47K OHM 1% 1/16W 0402 | RC0402FR-0747KL | https://www.digikey.com/en/products/detail/yageo/RC0402FR-07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
R3 | 1 | 24Ω 1% | RES 24 OHM 1% 1/16W 0402 | RC0402FR-0724RL | https://www.digikey.com/en/products/detail/yageo/RC0402FR-07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
R4 | 1 | 2kΩ | RES 2K OHM 5% 1/16W 0402 | RC0402JR-072KL | https://www.digikey.com/en/products/detail/yageo/RC0402JR-07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
R5 | 1 | 301Ω 1% | RES 301 OHM 1% 1/16W 0402 | RC0402FR-07301RL | https://www.digikey.com/en/products/detail/yageo/RC0402FR-07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
R6 | 1 | 316Ω 1% | RES 316 OHM 1% 1/16W 0402 | RC0402FR-07316RL | https://www.digikey.com/en/products/detail/yageo/RC0402FR-07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
R7 | 1 | 5.12kΩ | RES 5.1K OHM 1% 1/16W 0402 | RC0402FR-135K1L | https://www.digikey.com/en/products/detail/yageo/RC0402FR-13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
R10 | 1 | 51kΩ | RES 51K OHM 5% 1/16W 0402 | RC0402JR-0751KL | https://www.digikey.com/en/products/detail/yageo/RC0402JR-07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
R11 | 1 | 150Ω 1% | RES 150 OHM 1% 1/16W 0402 | RC0402FR-13150RL | https://www.digikey.com/en/products/detail/yageo/RC0402FR-13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
R12,R25,R29,R30 | 4 | 750Ω | RES 750 OHM 1% 1/16W 0402 | RC0402FR-13750RL | https://www.digikey.com/en/products/detail/yageo/RC0402FR-13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
R13,R14,R15,R16,R17,R18,R19,R20, R21,R22,R23,R24 | 12 | 51Ω | RES 51 OHM 1% 1/16W 0402 | RC0402FR-0751RL | https://www.digikey.com/en/products/detail/yageo/RC0402FR-07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
R26 | 1 | 130Ω 1% | RES 130 OHM 1% 1/8W 0805 | RC0805FR-07130RL | https://www.digikey.com/en/products/detail/yageo/RC0805FR-07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
R28 | 1 | 33Ω 1% | RES 33 OHM 1% 1/16W 0402 | RC0402FR-0733RL | https://www.digikey.com/en/products/detail/yageo/RC0402FR-07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
R31 | 1 | 390Ω 1% | RES 390 OHM 1% 1/8W 0805 | RC0805FR-07390RL | https://www.digikey.com/en/products/detail/yageo/RC0805FR-07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
R32,R33 | 2 | 4.7Ω | RES 4.7 OHM 5% 1/16W 0402 | RC0402JR-074R7L | https://www.digikey.com/en/products/detail/yageo/RC0402JR-07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
Cartridge Breakout Board
Reference | Quantity | Value | Description | Manufacter Part Number | Link
J1 | 1 |  | CONN FFC BOTTOM 40POS 0.5MM R/A | 5051104091 | https://www.digikey.com/en/products/detail/molex/5051104091/5254662
C1, C2 | 2 | 10µF | CAP CER 10UF 10V X5R 0402 | CL05A106MP5NUNC | https://www.digikey.com/en/products/detail/samsung-electro-m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
